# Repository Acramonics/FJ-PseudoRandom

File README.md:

FJ-PseudoRandom
===============

acramonics November 2026
------------------------

KiCad version of pseudo-random number generator from Anthony
Francis-Jones (@AnthonyFrancisJones on YouTube).

This is a 6-Stage Linear Feedback Shift Register [LFSR] pseudo-random
number generator.

Anthony asked on his [YouTube
video](https://www.youtube.com/watch?v=BzSbq5TuRcQ) whether anyone
would be prepared to create a PCB, so here it is.

- [Schematic](./FJ-Random_Schematic.pdf)
- [Bill of Materials](./FJ-Random_BOM.csv)
- [Gerber Files](./FJ-Random_Gerber.zip)

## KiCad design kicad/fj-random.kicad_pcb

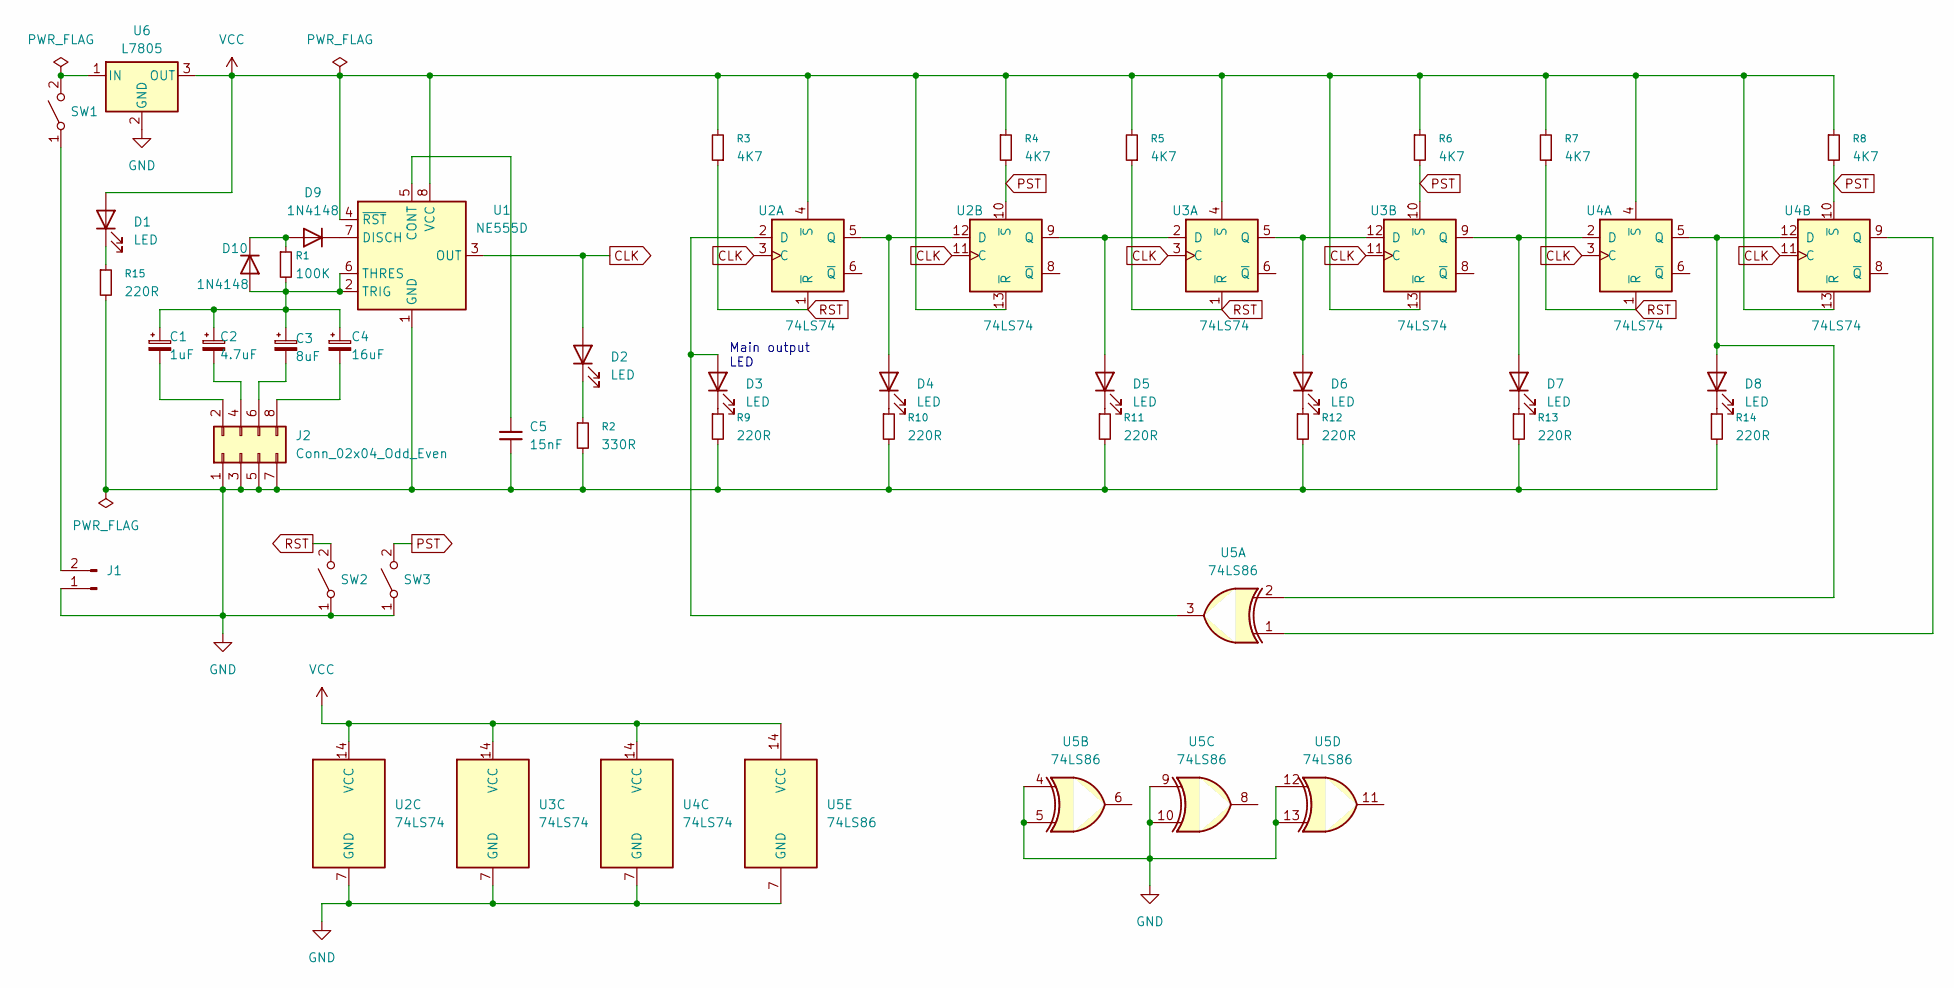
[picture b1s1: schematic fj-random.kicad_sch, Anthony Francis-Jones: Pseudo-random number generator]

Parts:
C1: 1uF; CP_Radial_D5.0mm_P2.50mm
C2: 4.7uF; CP_Radial_D5.0mm_P2.50mm
C3: 8uF; CP_Radial_D5.0mm_P2.50mm
C4: 16uF; CP_Radial_D5.0mm_P2.50mm
C5: 15nF; C_Disc_D3.4mm_W2.1mm_P2.50mm
D1, D2, D3, D4, D5, D6, D7, D8: LED; LED_D5.0mm
D9, D10: 1N4148; D_DO-35_SOD27_P2.54mm_Vertical_AnodeUp
J1: Conn_01x02_Pin; Molex_KK-254_AE-6410-02A_1x02_P2.54mm_Vertical
J2: Conn_02x04_Odd_Even; PinHeader_2x04_P2.54mm_Vertical
R1: 100K; R_Axial_DIN0309_L9.0mm_D3.2mm_P2.54mm_Vertical
R2: 330R; R_Axial_DIN0309_L9.0mm_D3.2mm_P2.54mm_Vertical
R3, R4, R5, R6, R7, R8: 4K7; R_Axial_DIN0207_L6.3mm_D2.5mm_P10.16mm_Horizontal
R9, R10, R11, R12, R13, R14, R15: 220R; R_Axial_DIN0207_L6.3mm_D2.5mm_P10.16mm_Horizontal
SW1: SW_SPST; SPDT_SlideSwitch_P2.54
SW2, SW3: SW_SPST; SW_TH_Tactile_Omron_B3F-100x
U1: NE555D; DIP-8_W7.62mm
U2, U3, U4: 74LS74; DIP-14_W7.62mm
U5: 74LS86; DIP-14_W7.62mm
U6: L7805; TO-220-3_Vertical

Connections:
CLK: D2.2 (A), U1.3 (OUT), U2.3 (C), U2.11 (C), U3.3 (C), U3.11 (C), U4.3 (C), U4.11 (C)
GND: C5.2, J1.1, J2.1, J2.3, J2.5, J2.7, R2.2, R9.2, R10.2, R11.2, R12.2, R13.2, R14.2, R15.2, SW2.1 (A), SW3.1 (A), U1.1 (GND), U2.7 (GND), U3.7 (GND), U4.7 (GND), U5.4, U5.5, U5.7 (GND), U5.9, U5.10, U5.12, U5.13, U6.2 (GND)
unnamed: D1.1 (K), R15.1
unnamed: D2.1 (K), R2.1
unnamed: D3.2 (A), U2.2 (D), U5.3
unnamed: D3.1 (K), R9.1
unnamed: D4.2 (A), U2.5 (Q), U2.12 (D)
unnamed: D4.1 (K), R10.1
unnamed: D5.2 (A), U2.9 (Q), U3.2 (D)
unnamed: D5.1 (K), R11.1
unnamed: D6.2 (A), U3.5 (Q), U3.12 (D)
unnamed: D6.1 (K), R12.1
unnamed: D7.2 (A), U3.9 (Q), U4.2 (D)
unnamed: D7.1 (K), R13.1
unnamed: D8.2 (A), U4.5 (Q), U4.12 (D), U5.2
unnamed: D8.1 (K), R14.1
unnamed: D9.1 (K), U1.7 (DISCH)
unnamed: C1.1, C2.1, C3.1, C4.1, D10.2 (A), R1.2, U1.2 (TRIG), U1.6 (THRES)
unnamed: D9.2 (A), D10.1 (K), R1.1
unnamed: J1.2, SW1.1 (A)
unnamed: C1.2, J2.2
unnamed: C2.2, J2.4
unnamed: C3.2, J2.6
unnamed: C4.2, J2.8
unnamed: SW1.2 (B), U6.1 (IN)
unnamed: C5.1, U1.5 (CONT)
unnamed: U4.9 (Q), U5.1
PST: R4.2, R6.2, R8.2, SW3.2 (B), U2.10 (~S), U3.10 (~S), U4.10 (~S)
RST: R3.1, R5.1, R7.1, SW2.2 (B), U2.1 (~R), U3.1 (~R), U4.1 (~R)
VCC: D1.2 (A), R3.2, R4.1, R5.2, R6.1, R7.2, R8.1, U1.4 (~RST), U1.8 (VCC), U2.4 (~S), U2.13 (~R), U2.14 (VCC), U3.4 (~S), U3.13 (~R), U3.14 (VCC), U4.4 (~S), U4.13 (~R), U4.14 (VCC), U5.14 (VCC), U6.3 (OUT)

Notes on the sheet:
Main output LED

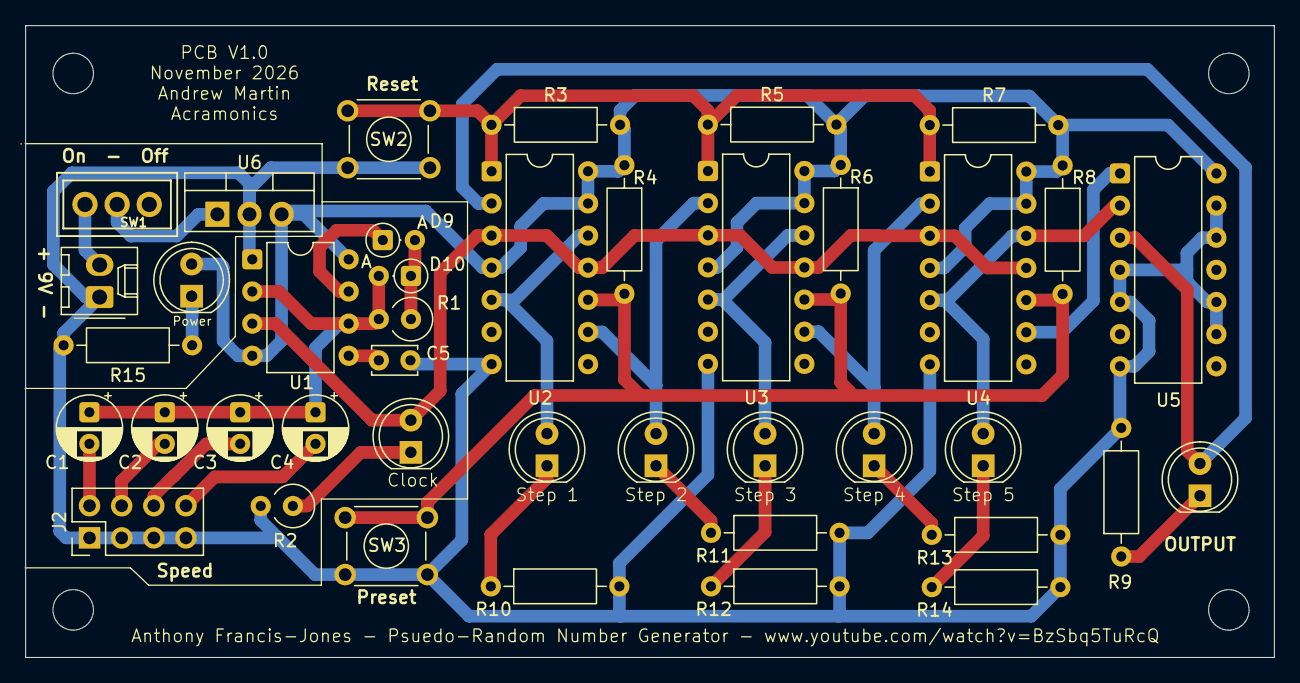
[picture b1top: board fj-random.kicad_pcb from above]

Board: 2 copper layers, 98.7 x 49.9 mm, 41 parts (0 on the bottom side), 30 nets.

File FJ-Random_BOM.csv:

Reference,Qty,Value,Notes,Comments
,,,,
C1,1,1uF,Electrolytic D5.0mm P2.50mm,
C2,1,4.7uF,Electrolytic D5.0mm P2.50mm,
C3,1,8uF,Electrolytic D5.0mm P2.50mm,
C4,1,16uF,Electrolytic D5.0mm P2.50mm,
C5,1,15nF,Ceramic Disc P2.50mm,
"D1,D2,D3,D4,D5,D6,D7,D8",8,LED,5mm LED,
"D9,D10",2,1N4148,DO-34,
J1,1,Conn_01x02_Pin,Molex KK-254 2-pin Pitch 2.54mm,
J2,1,Conn_02x04_Odd_Even,PinHeader 2x4 rows Pitch 2.54mm,
R1,1,100K,,
R2,1,330R,,
"R3,R4,R5,R6,R7,R8",6,4K7,,
"R9,R10,R11,R12,R13,R14,R15",7,220R,,
SW1,1,SW_SPDT,PCB mount slide-switch Pitch 2.54mm,e.g. Buwei SPDT 1P2T 3 Pin PCB Vertical Slide Switch SS12D00G3 https://www.amazon.co.uk/dp/B08MZJBJWR/
"SW2,SW3",2,SW_SPST,Through-hole Button Switch 6x6x4.3 (Omron_B3F-100x),e.g. AliExpress G89 Tactile Tact Push Button Micro Switch https://www.aliexpress.com/item/1005009810819149.html
U1,1,NE555D,DIP8,
"U2,U3,U4",3,74LS74,DIP14,
U5,1,74LS86,DIP14,
U6,1,L7805,TO-220-3,
